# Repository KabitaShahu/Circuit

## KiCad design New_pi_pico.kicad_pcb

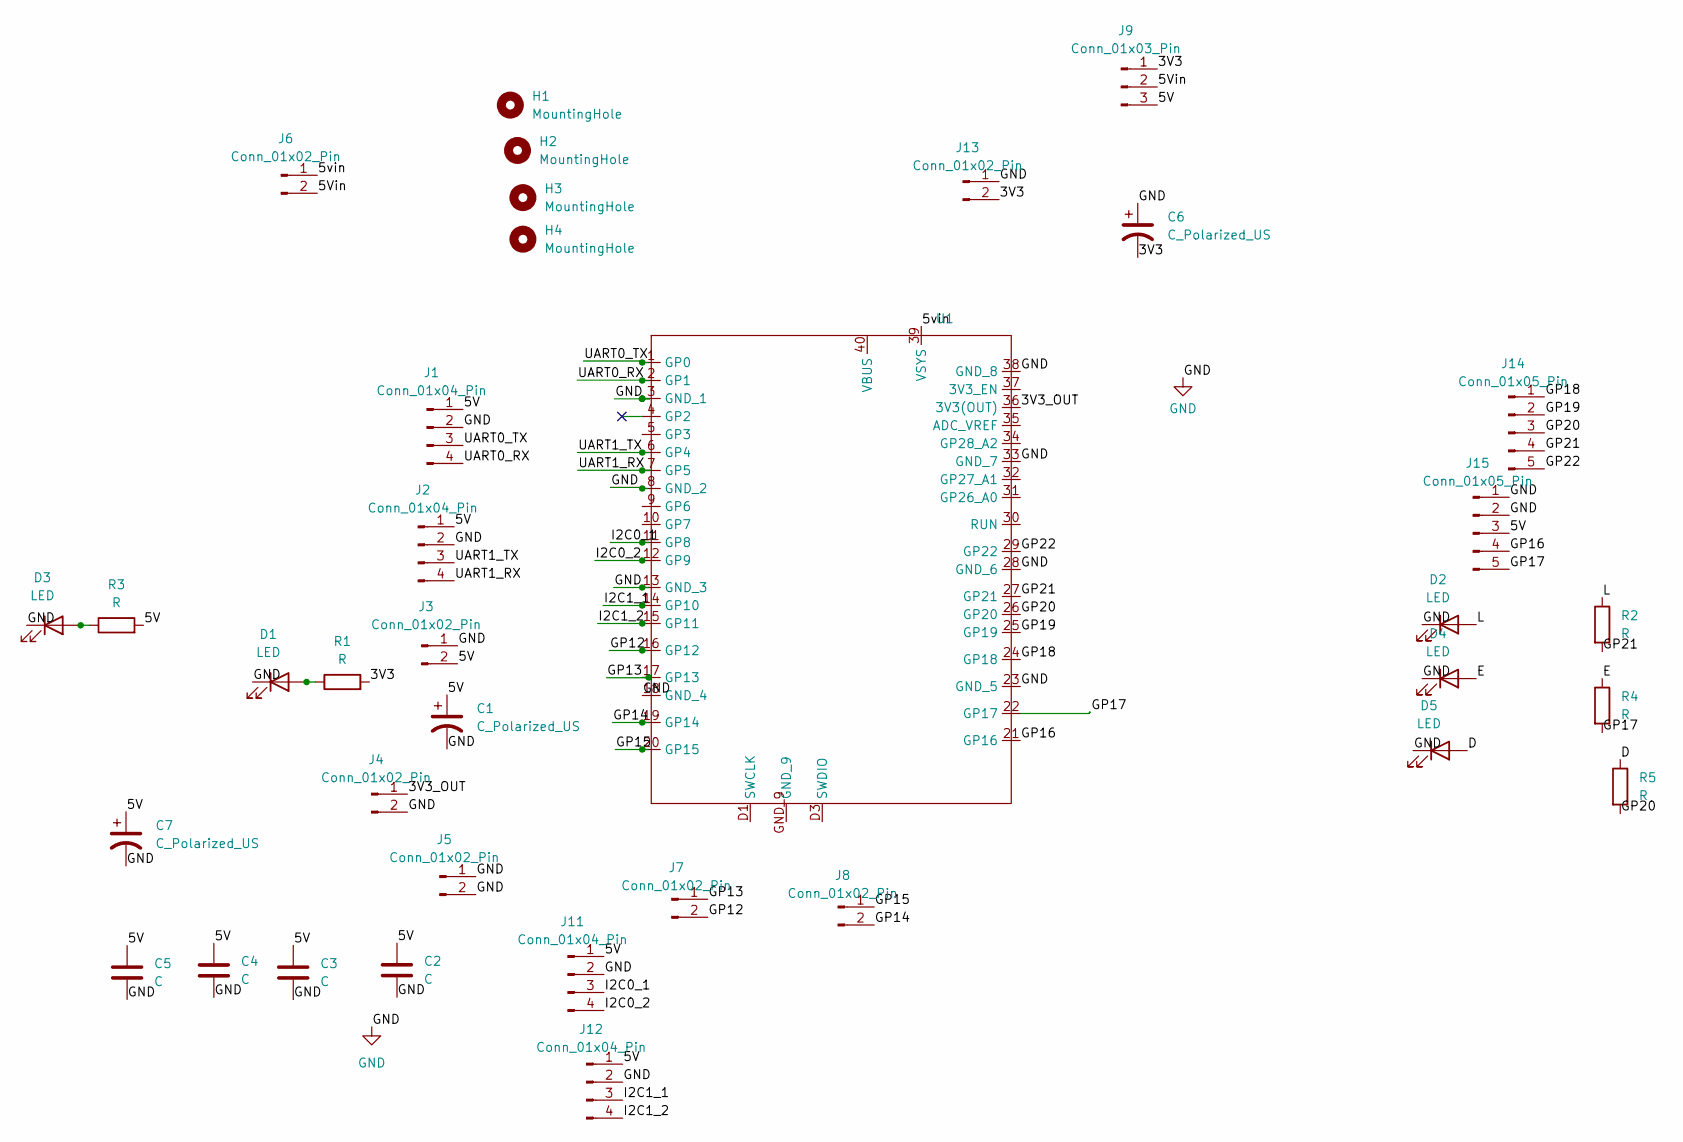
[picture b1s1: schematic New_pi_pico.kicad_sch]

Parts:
C1: C_Polarized_US; Capacitor_100uF
C2, C3, C4, C5: C; Capacitor_Disc_Small
C6, C7: C_Polarized_US; Capacitor_Disc_Small
D1, D2, D3, D4, D5: LED; LED_D3.0mm
H1, H2, H3, H4: MountingHole; MountingHole_3mm_Pad
J1, J2, J11, J12: Conn_01x04_Pin; jst_4
J3, J13: Conn_01x02_Pin; Connector_Bornier_2
J4, J5, J7, J8: Conn_01x02_Pin; JST_EH_B2B-EH-A_1x02_P2.50mm_Vertical
J6: Conn_01x02_Pin; KD1-101F_small
J9: Conn_01x03_Pin; SWITCH
J14, J15: Conn_01x05_Pin; JST_EH_B5B-EH-A_1x05_P2.50mm_Vertical
R1, R2, R3, R4, R5: R; Resistor_small
U1: pi_pico

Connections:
/3V3: C6.2, J9.1, J13.2, R1.2
/3V3_OUT: J4.1, U1.36 (3V3(OUT))
/5V: C1.1, C2.1, C3.1, C4.1, C5.1, C7.1, J1.1, J2.1, J3.2, J9.3, J11.1, J12.1, J15.3, R3.2
/5Vin: J6.2, J9.2
/5vin: J6.1, U1.39 (VSYS)
/D: D5.2 (A), R5.1
/E: D4.2 (A), R4.1
/GP12: J7.2, U1.16 (GP12)
/GP13: J7.1, U1.17 (GP13)
/GP14: J8.2, U1.19 (GP14)
/GP15: J8.1, U1.20 (GP15)
/GP16: J15.4, U1.21 (GP16)
/GP17: J15.5, R4.2, U1.22 (GP17)
/GP18: J14.1, U1.24 (GP18)
/GP19: J14.2, U1.25 (GP19)
/GP20: J14.3, R5.2, U1.26 (GP20)
/GP21: J14.4, R2.2, U1.27 (GP21)
/GP22: J14.5, U1.29 (GP22)
/I2C0_1: J11.3, U1.11 (GP8)
/I2C0_2: J11.4, U1.12 (GP9)
/I2C1_1: J12.3, U1.14 (GP10)
/I2C1_2: J12.4, U1.15 (GP11)
/L: D2.2 (A), R2.1
/UART0_RX: J1.4, U1.2 (GP1)
/UART0_TX: J1.3, U1.1 (GP0)
/UART1_RX: J2.4, U1.7 (GP5)
/UART1_TX: J2.3, U1.6 (GP4)
GND: C1.2, C2.2, C3.2, C4.2, C5.2, C6.1, C7.2, D1.1 (K), D2.1 (K), D3.1 (K), D4.1 (K), D5.1 (K), J1.2, J2.2, J3.1, J4.2, J5.1, J5.2, J11.2, J12.2, J13.1, J15.1, J15.2, U1.3 (GND_1), U1.8 (GND_2), U1.13 (GND_3), U1.18 (GND_4), U1.23 (GND_5), U1.28 (GND_6), U1.33 (GND_7), U1.38 (GND_8)
unnamed: D1.2 (A), R1.1
unnamed: D3.2 (A), R3.1

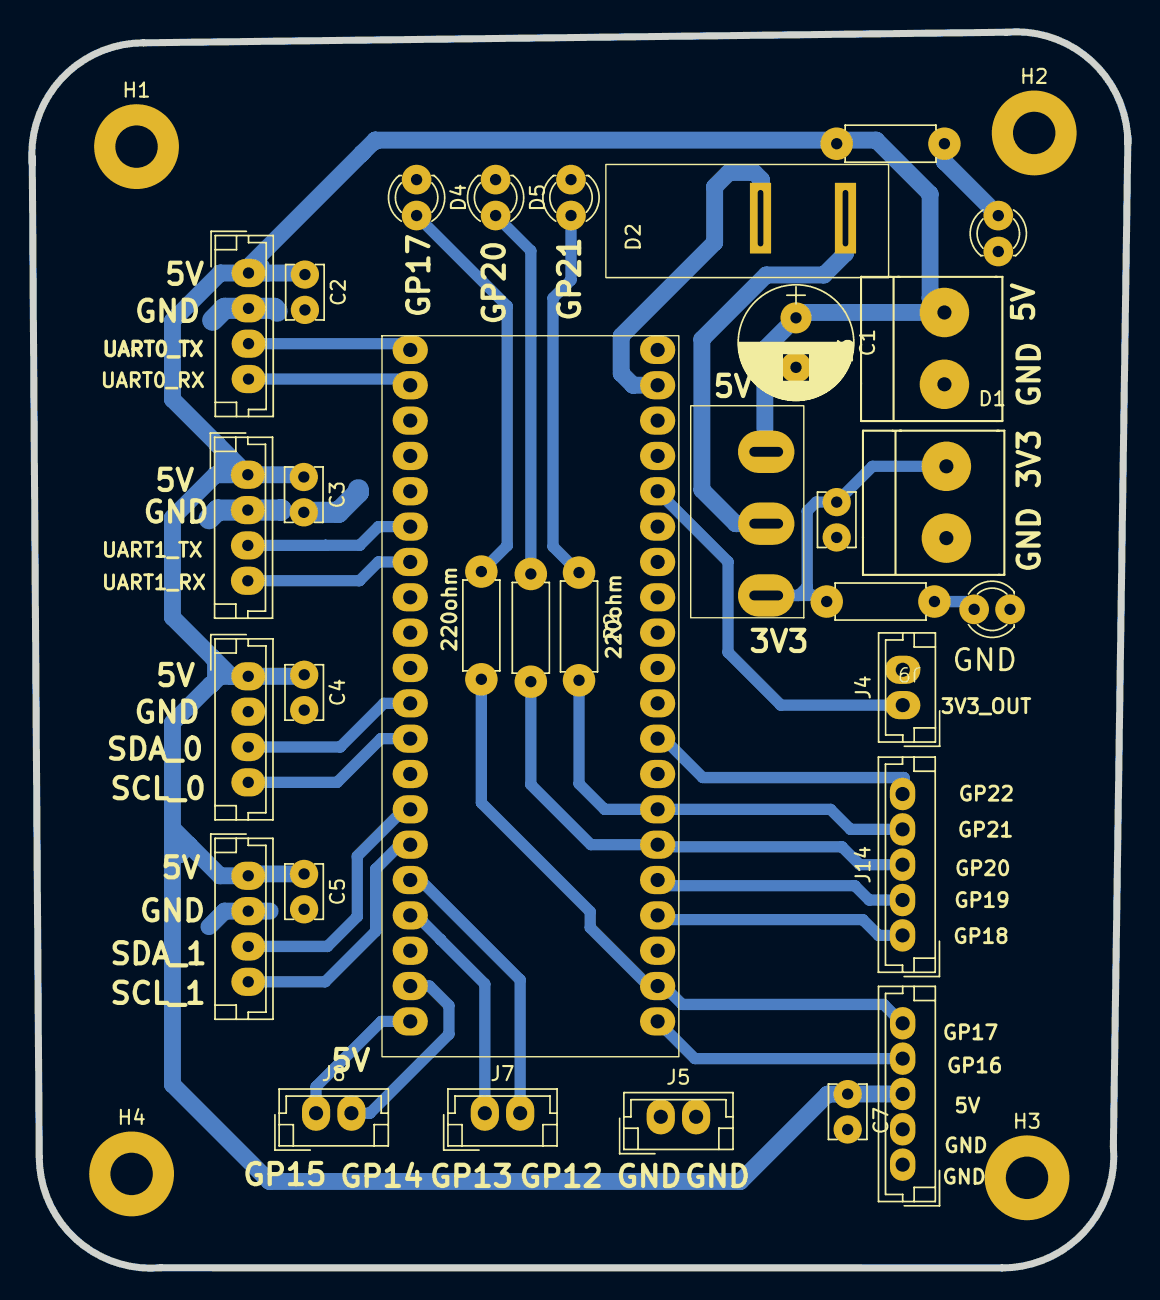
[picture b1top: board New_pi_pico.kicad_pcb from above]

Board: 2 copper layers, 77.5 x 87.5 mm, 36 parts (0 on the bottom side), 30 nets.

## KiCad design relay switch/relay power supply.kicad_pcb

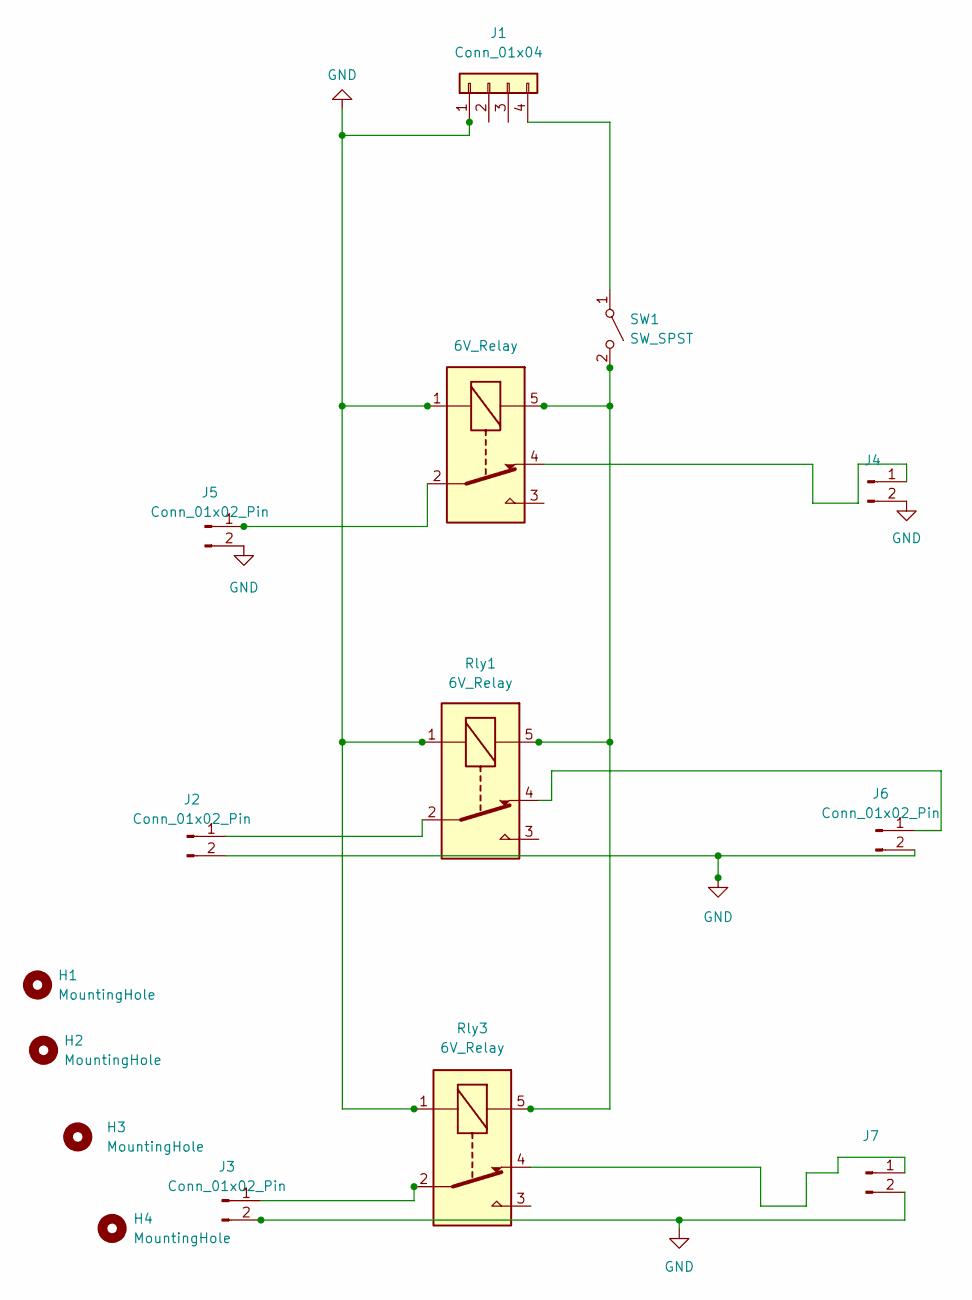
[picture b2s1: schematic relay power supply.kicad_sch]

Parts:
H1, H2, H3, H4: MountingHole; MountingHole_3mm_Pad
J1: Conn_01x04; jst_4
J2, J3, J4, J5, J6, J7: Conn_01x02_Pin; Solar_Connector
Rly1, Rly2, Rly3: 6V_Relay; HLS relay
SW1: SW_SPST; Solar_Connector

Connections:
GND: J1.1, J2.2, J3.2, J4.2, J5.2, J6.2, J7.2, Rly1.1, Rly2.1, Rly3.1
unnamed: J1.4, SW1.1 (A)
unnamed: J2.1, Rly1.2
unnamed: J3.1, Rly3.2
unnamed: J4.1, Rly2.4
unnamed: J5.1, Rly2.2
unnamed: J6.1, Rly1.4
unnamed: J7.1, Rly3.4
unnamed: Rly1.5, Rly2.5, Rly3.5, SW1.2 (B)

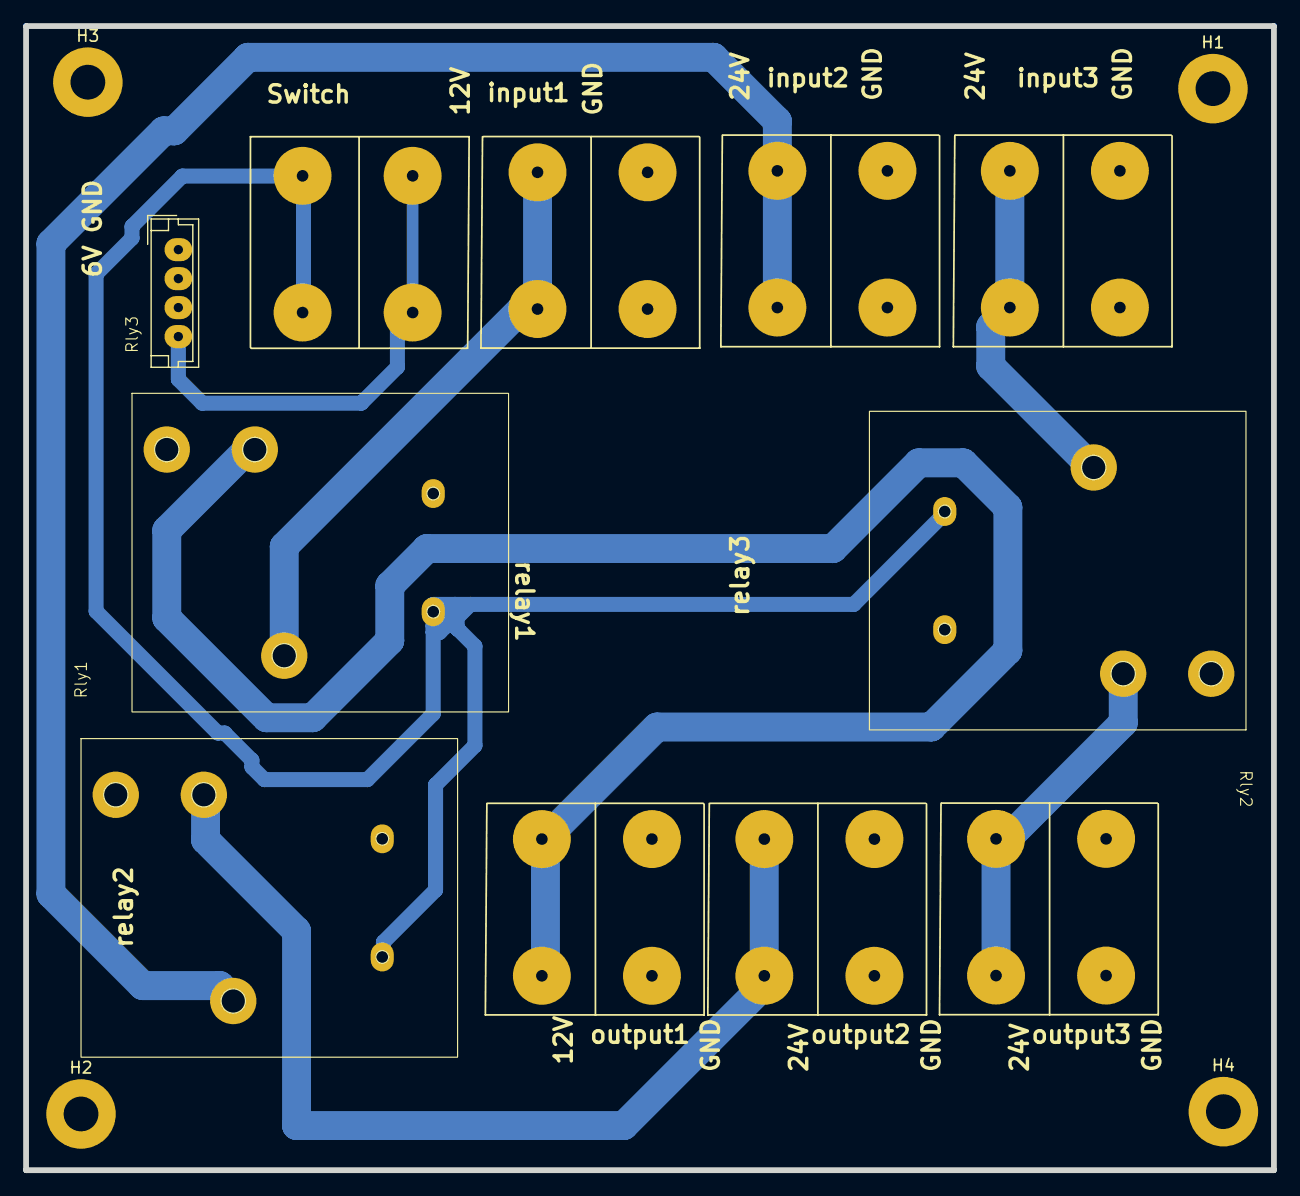
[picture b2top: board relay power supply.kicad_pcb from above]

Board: 2 copper layers, 107.7 x 98.8 mm, 15 parts (0 on the bottom side), 9 nets.

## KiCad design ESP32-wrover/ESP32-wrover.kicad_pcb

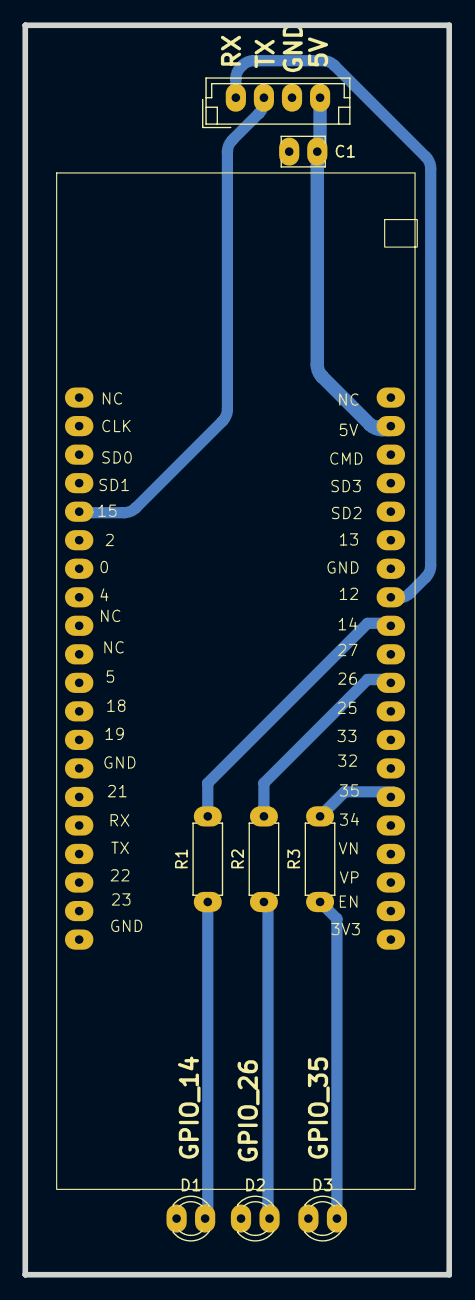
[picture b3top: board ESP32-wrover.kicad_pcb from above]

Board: 2 copper layers, 37.8 x 111.2 mm, 9 parts (0 on the bottom side), 10 nets.

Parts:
C1: C; Capacitor_Disc_Small
D1, D2, D3: LED; LED_D3.0mm
ESP32T1: ESP32_T18 - 3.0; ESP32_T18-3.0
J1: Conn_01x04_Pin; jst_4
R1, R2, R3: R; Resistor_small

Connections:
+5V: C1.1, ESP32T1.5V (CMD), J1.4
/1: D1.2 (A), R1.1
/2: D2.2 (A), R2.1
/3: D3.2 (A), R3.1
/LED1: ESP32T1.14 (GND), R1.2
/LED2: ESP32T1.26 (33), R2.2
/LED3: ESP32T1.35 (22), R3.2
/RX: ESP32T1.15 (4), J1.2
/TX: ESP32T1.12 (13), J1.1
GND: C1.2, D1.1 (K), D2.1 (K), D3.1 (K), ESP32T1.GND (SD3), J1.3

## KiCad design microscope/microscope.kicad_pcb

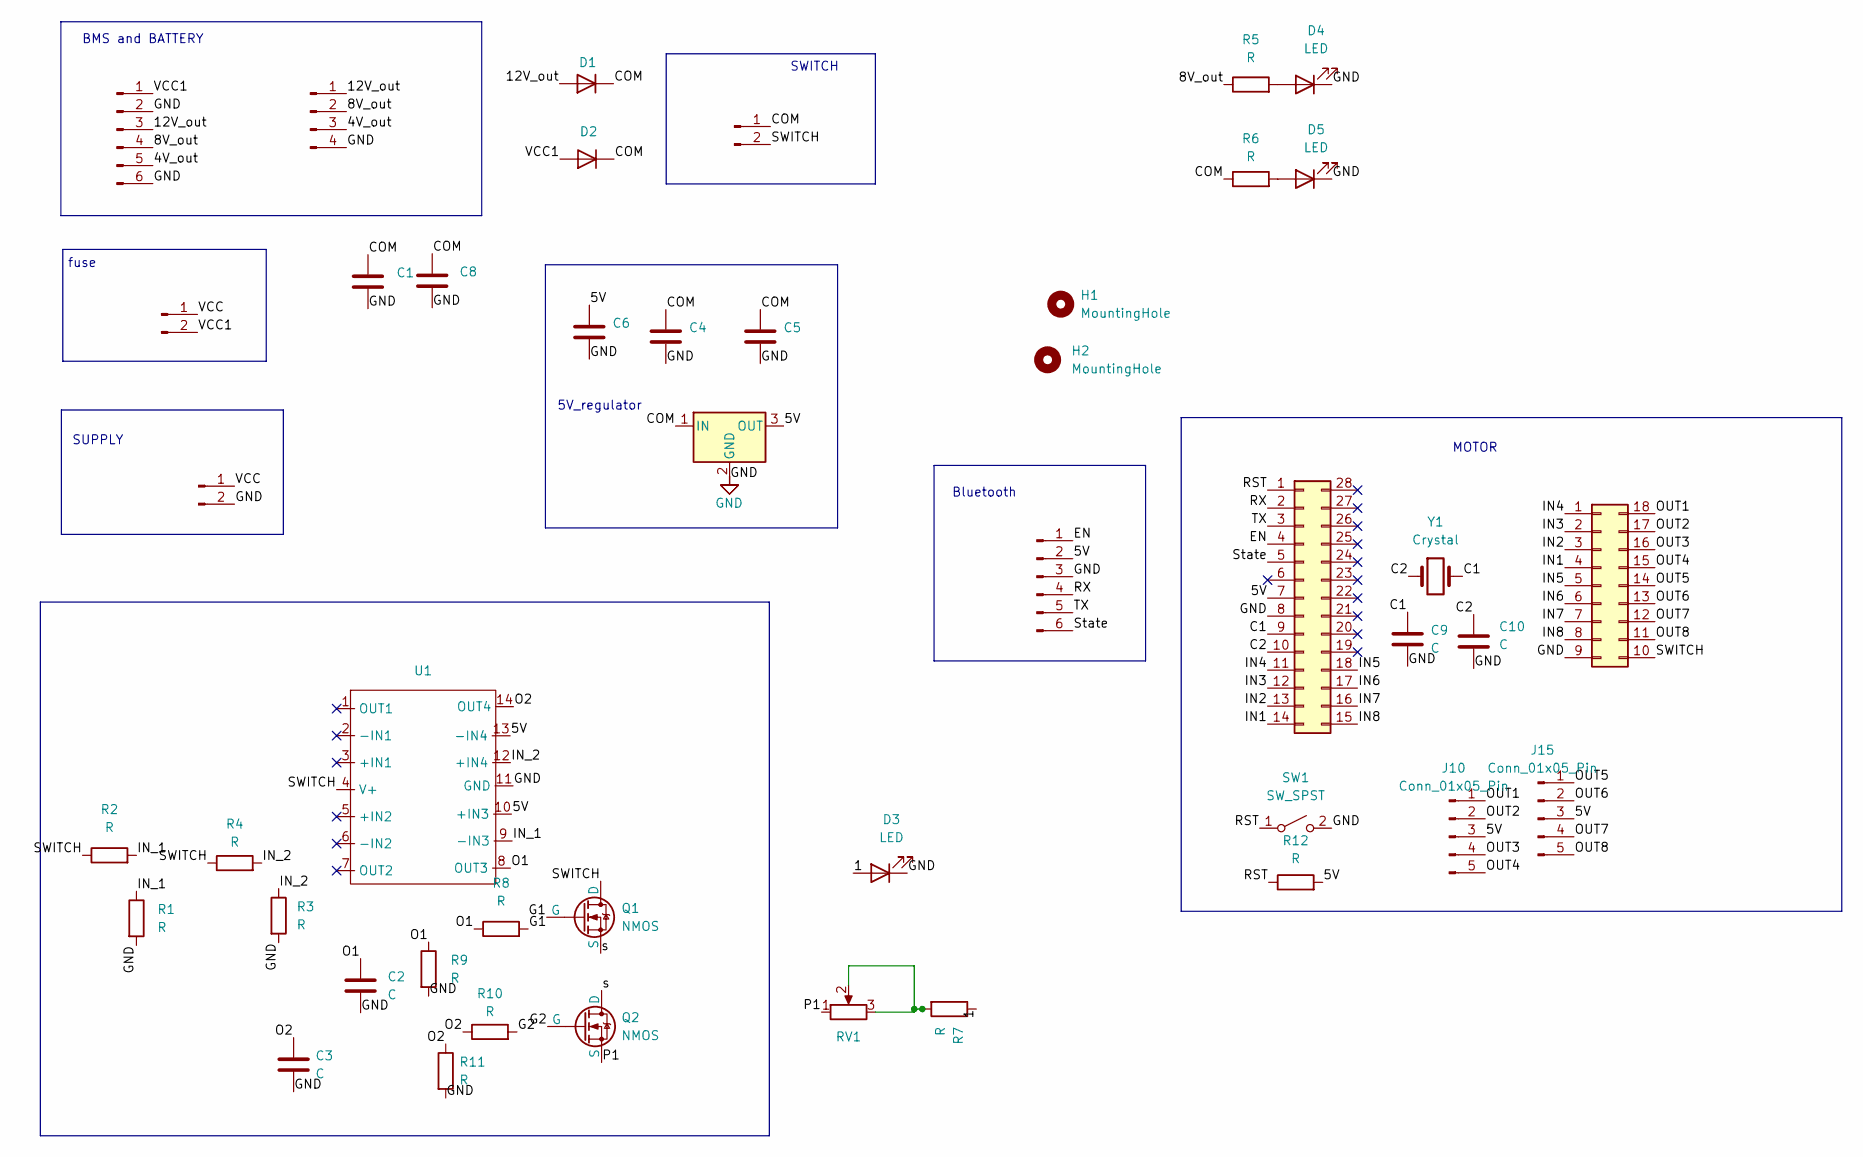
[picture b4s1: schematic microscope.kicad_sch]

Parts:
C1, C2, C3, C5, C9, C10: C; Capacitor_Disc_Small
C4, C8: C; Capacitor_100uF
C6: C; Capacitor_10uF
D1, D2: 1N914; Diode_Medium
D3, D4, D5: LED; bornier2
H1, H2: MountingHole; MountingHole_3mm
J1, J2, J6: Conn_01x02_Pin; bornier2
J5: Conn_01x04_Pin; new_5_jst_bournier
J7: Conn_02x14_Counter_Clockwise; DIP-28
J8: Conn_02x09_Counter_Clockwise; DIP-18_W7.62mm_LongPads
J9: Conn_01x06_Pin; PinHeader_1x06_P2.54mm_Vertical
J10, J15: Conn_01x05_Pin; new_5_jst_bournier
J11: Conn_01x06_Pin; BMS
Q1, Q2: NMOS; TO-220-3_Vertical
R1, R2, R3, R4, R5, R6, R8, R9, R10, R11, R12: R; Resistor_small
R7: R; R_Axial_DIN0516_L15.5mm_D5.0mm_P20.32mm_Horizontal
RV1: R_Potentiometer; bornier2
SW1: SW_SPST; Push_Button
U1: DIP-14_W7.62mm
U2: L7805; Voltage_Regulators
Y1: Crystal

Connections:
/1: D3.2 (A), R7.1
/4V_out: J5.3, J11.5
/5V: C6.1, J7.7, J9.2, J10.3, J15.3, R12.2, U1.10 (+IN3), U1.13 (-IN4), U2.3 (OUT)
/8V_out: J5.2, J11.4, R5.1
/12V_out: D1.2 (A), J5.1, J11.3
/C1: C9.1, J7.9, Y1.2
/C2: C10.1, J7.10, Y1.1
/COM: C1.1, C4.1, C5.1, C8.1, D1.1 (K), D2.1 (K), J6.1, R6.1, U2.1 (IN)
/EN: J7.4, J9.1
/G1: Q1.2 (G), R8.2
/G2: Q2.2 (G), R10.2
/IN1: J7.14, J8.4
/IN2: J7.13, J8.3
/IN3: J7.12, J8.2
/IN4: J7.11, J8.1
/IN5: J7.18, J8.5
/IN6: J7.17, J8.6
/IN7: J7.16, J8.7
/IN8: J7.15, J8.8
/IN_1: R1.1, R2.2, U1.9 (-IN3)
/IN_2: R3.1, R4.2, U1.12 (+IN4)
/O1: C2.1, R8.1, R9.1, U1.8 (OUT3)
/O2: C3.1, R10.1, R11.1, U1.14 (OUT4)
/OUT1: J8.18, J10.1
/OUT2: J8.17, J10.2
/OUT3: J8.16, J10.4
/OUT4: J8.15, J10.5
/OUT5: J8.14, J15.1
/OUT6: J8.13, J15.2
/OUT7: J8.12, J15.4
/OUT8: J8.11, J15.5
/P1: Q2.3 (S), RV1.1
/RST: J7.1, R12.1, SW1.1 (A)
/RX: J7.2, J9.4
/SWITCH: J6.2, J8.10, Q1.1 (D), R2.1, R4.1, U1.4 (V+)
/State: J7.5, J9.6
/TX: J7.3, J9.5
/VCC: J1.1, J2.1
/VCC1: D2.2 (A), J2.2, J11.1
/s: Q1.3 (S), Q2.1 (D)
GND: C1.2, C2.2, C3.2, C4.2, C5.2, C6.2, C8.2, C9.2, C10.2, D3.1 (K), D4.1 (K), D5.1 (K), J1.2, J5.4, J7.8, J8.9, J9.3, J11.2, J11.6, R1.2, R3.2, R9.2, R11.2, SW1.2 (B), U1.11 (GND), U2.2 (GND)
unnamed: D4.2 (A), R5.2
unnamed: D5.2 (A), R6.2
unnamed: R7.2, RV1.2, RV1.3

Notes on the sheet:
fuse
Bluetooth
MOTOR
SUPPLY
5V_regulator
SWITCH
BMS and BATTERY

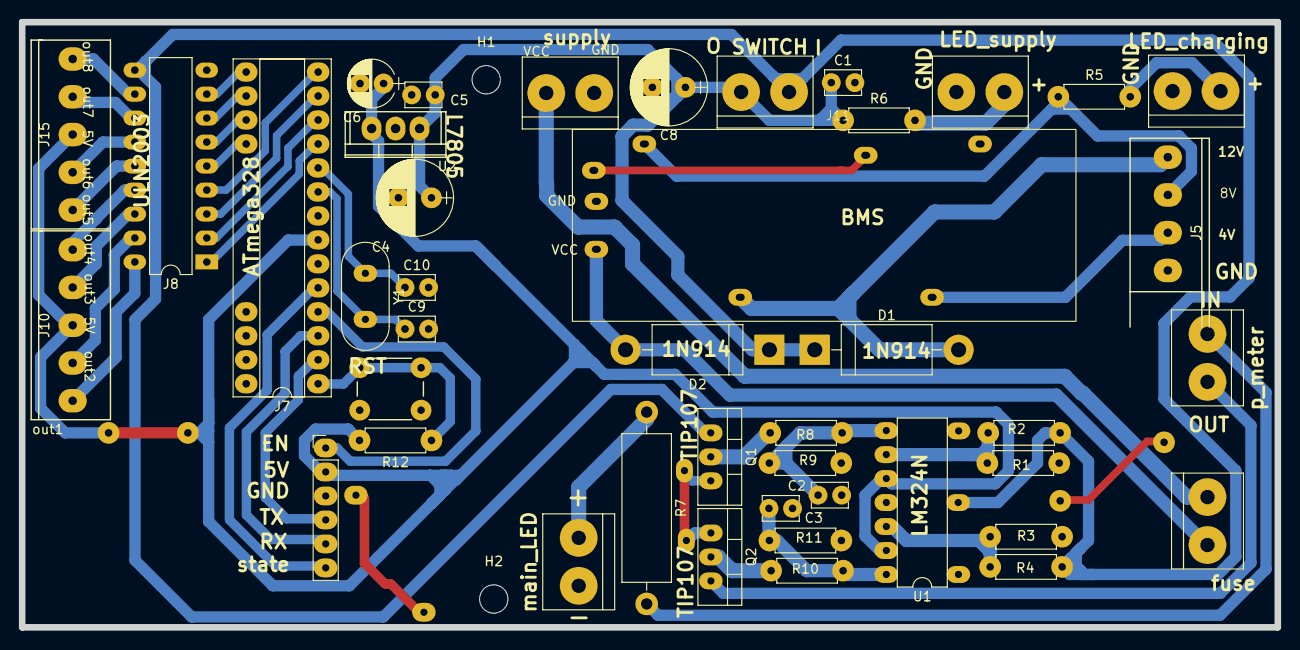
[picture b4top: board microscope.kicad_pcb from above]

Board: 2 copper layers, 133.0 x 64.1 mm, 45 parts (0 on the bottom side), 44 nets.

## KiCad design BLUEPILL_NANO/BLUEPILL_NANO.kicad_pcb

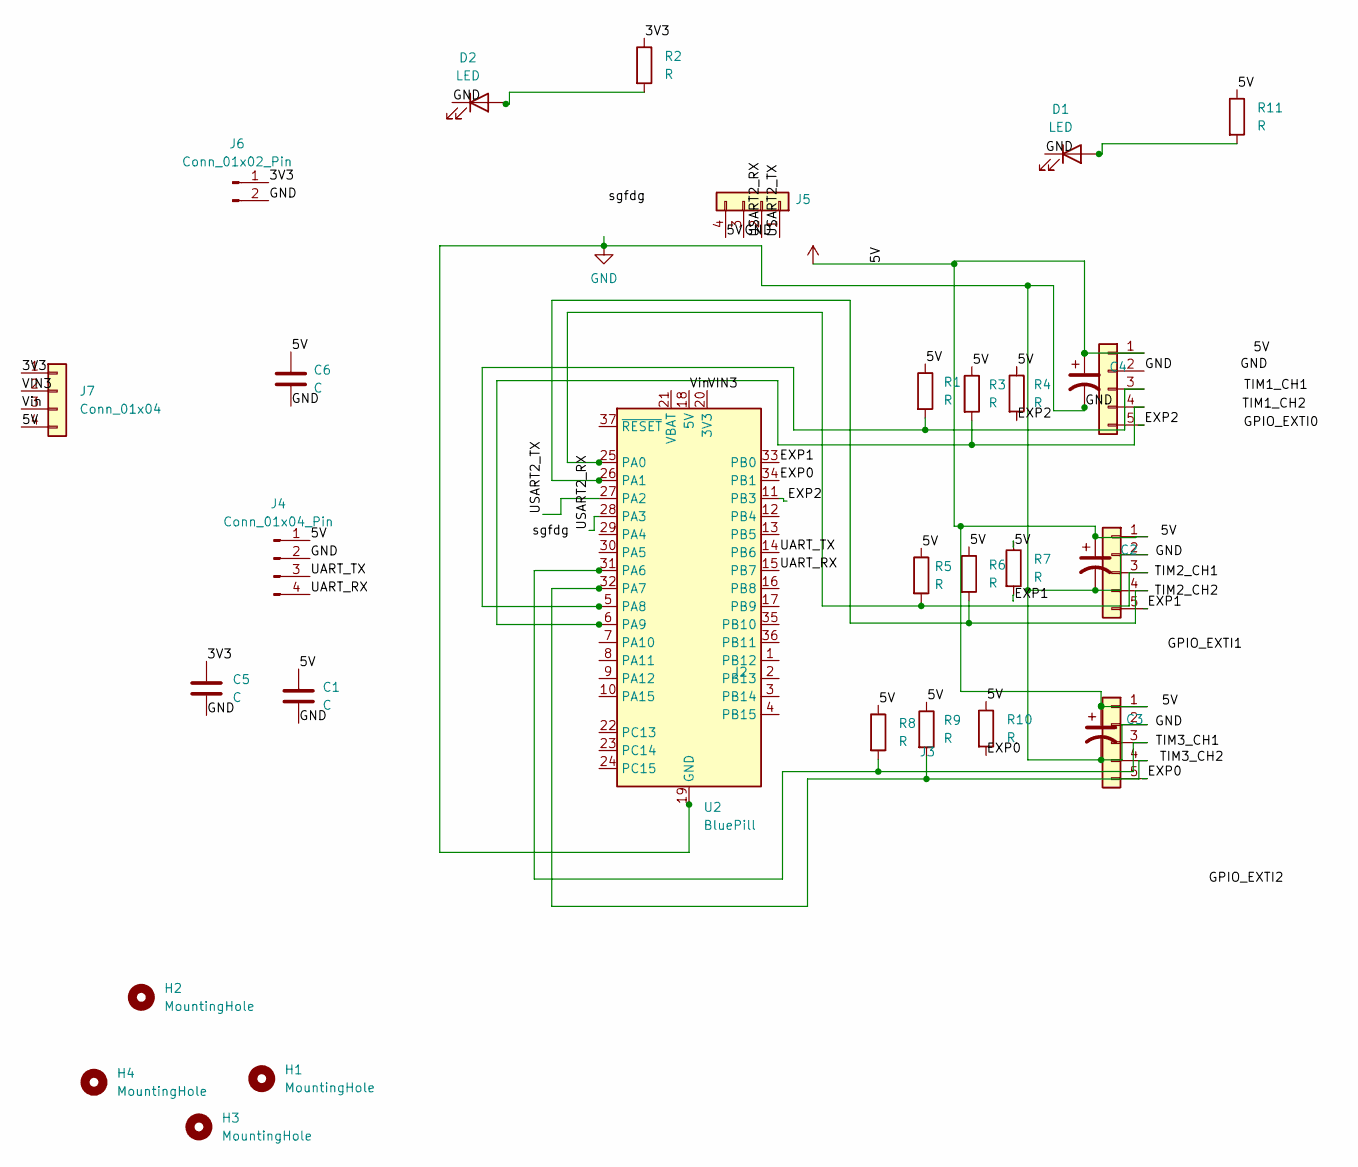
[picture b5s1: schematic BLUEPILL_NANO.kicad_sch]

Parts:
C1: C; Capacitor_100uF
C2, C3, C4: C_Polarized_US; Capacitor_Disc_Small
C5: C; Capacitor_10uF
C6: C; Capacitor_Disc_Small
D1, D2: LED; LED_D3.0mm
H1, H2, H3, H4: MountingHole; MountingHole_2.5mm_Pad
J1, J2, J3: Conn_01x05; JST_EH_B5B-EH-A_1x05_P2.50mm_Vertical
J4: Conn_01x04_Pin; jst_4
J5: Conn_01x04; jst_4
J6: Conn_01x02_Pin; JST_EH_B2B-EH-A_1x02_P2.50mm_Vertical
J7: Conn_01x04; PinHeader_1x04_P2.54mm_Vertical
R1, R2, R3, R4, R5, R6, R7, R8, R9, R10, R11: R; Resistor_small
U2: BluePill; STM32_BLUEPLL_MOD

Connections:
+5V: C1.1, C2.1, C3.1, C4.1, C6.1, J1.1, J2.1, J3.1, J4.1, J5.4, J7.4, R1.1, R3.1, R4.1, R5.1, R6.1, R7.1, R8.1, R9.1, R10.1, R11.1
/3V3: C5.1, J6.1, J7.1, R2.1
/EXP0: J3.5, R10.2, U2.34 (PB1)
/EXP1: J2.5, R7.2, U2.33 (PB0)
/EXP2: J1.5, R4.2, U2.11 (PB3)
/UART_RX: J4.4, U2.15 (PB7)
/UART_TX: J4.3, U2.14 (PB6)
/USART2_RX: J5.2, U2.28 (PA3)
/USART2_TX: J5.1, U2.27 (PA2)
/VIN3: J7.2, U2.20 (3V3), U2.38 (3V3)
/Vin: J7.3, U2.18 (5V)
GND: C1.2, C2.2, C3.2, C4.2, C5.2, C6.2, D1.1 (K), D2.1 (K), J1.2, J2.2, J3.2, J4.2, J5.3, J6.2, U2.19 (GND), U2.39 (GND), U2.40 (GND)
unnamed: D1.2 (A), R11.2
unnamed: D2.2 (A), R2.2
unnamed: J1.3, R1.2, U2.5 (PA8)
unnamed: J1.4, R3.2, U2.6 (PA9)
unnamed: J2.3, R5.2, U2.25 (PA0)
unnamed: J2.4, R6.2, U2.26 (PA1)
unnamed: J3.3, R8.2, U2.31 (PA6)
unnamed: J3.4, R9.2, U2.32 (PA7)

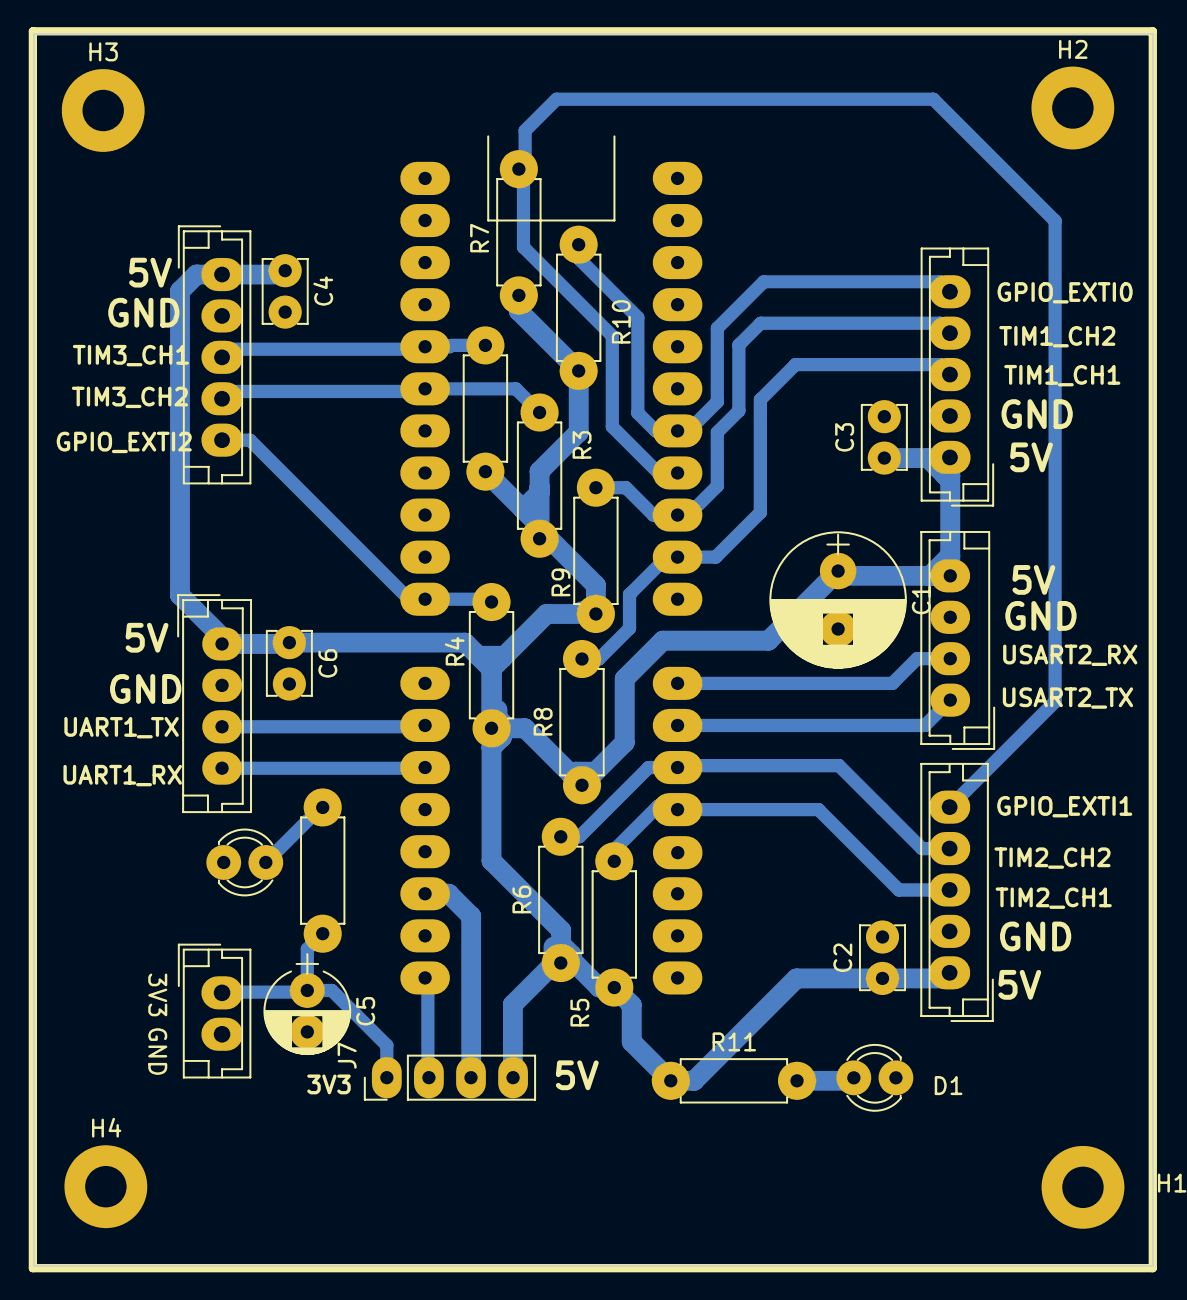
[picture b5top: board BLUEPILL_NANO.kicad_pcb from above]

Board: 2 copper layers, 67.5 x 74.4 mm, 31 parts (0 on the bottom side), 20 nets.

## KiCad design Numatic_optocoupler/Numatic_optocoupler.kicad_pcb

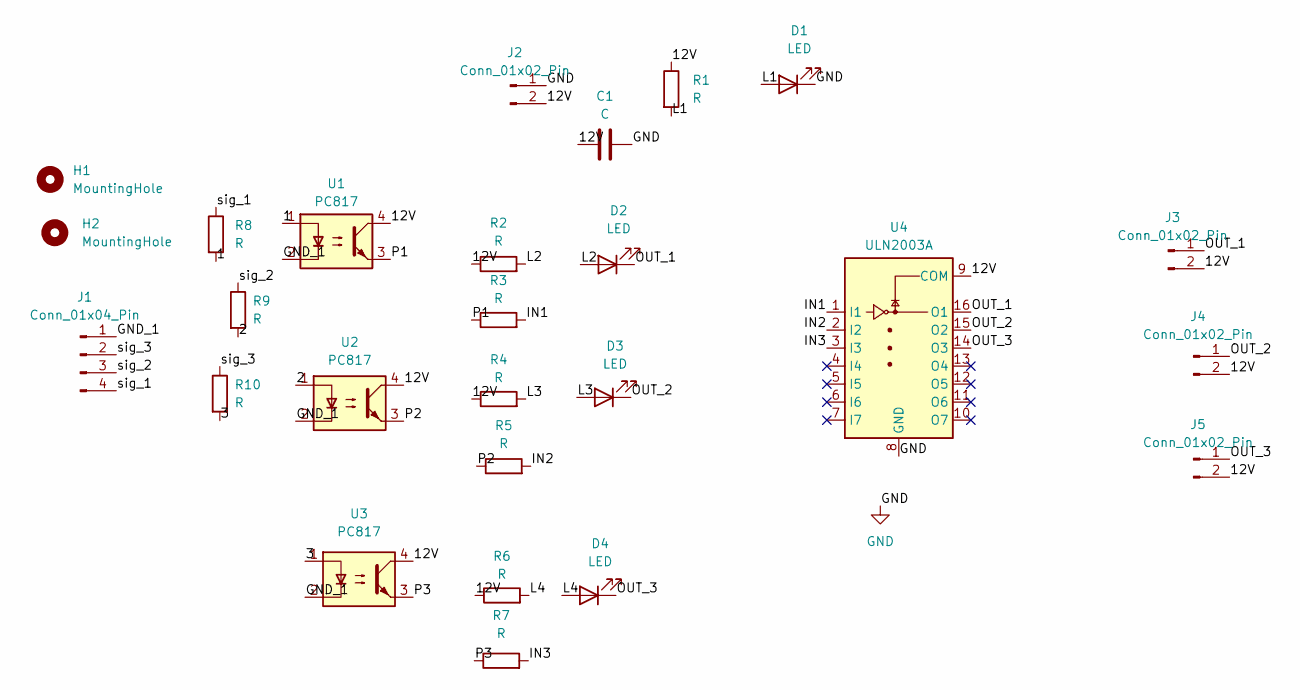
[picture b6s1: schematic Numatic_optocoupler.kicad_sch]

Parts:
C1: C; Capacitor_100uF
D1, D2, D3, D4: LED; LED_D3.0mm
H1, H2: MountingHole; MountingHole_3mm
J1: Conn_01x04_Pin; jst_4
J2, J3, J4, J5: Conn_01x02_Pin; bornier2
R1, R2, R3, R4, R5, R6, R7, R8, R9, R10: R; Resistor_small
U1, U2, U3: PC817; DIP-4_W7.62mm
U4: ULN2003A; DIP-16_W7.62mm_LongPads

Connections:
/1: R8.2, U1.1
/2: R9.2, U2.1
/3: R10.2, U3.1
/12V: C1.2, J2.2, J3.2, J4.2, J5.2, R1.1, R2.1, R4.1, R6.1, U1.4, U2.4, U3.4, U4.9 (COM)
/GND_1: J1.1, U1.2, U2.2, U3.2
/IN1: R3.2, U4.1 (I1)
/IN2: R5.2, U4.2 (I2)
/IN3: R7.2, U4.3 (I3)
/L1: D1.2 (A), R1.2
/L2: D2.2 (A), R2.2
/L3: D3.2 (A), R4.2
/L4: D4.2 (A), R6.2
/OUT_1: D2.1 (K), J3.1, U4.16 (O1)
/OUT_2: D3.1 (K), J4.1, U4.15 (O2)
/OUT_3: D4.1 (K), J5.1, U4.14 (O3)
/P1: R3.1, U1.3
/P2: R5.1, U2.3
/P3: R7.1, U3.3
/sig_1: J1.4, R8.1
/sig_2: J1.3, R9.1
/sig_3: J1.2, R10.1
GND: C1.1, D1.1 (K), J2.1, U4.8 (GND)

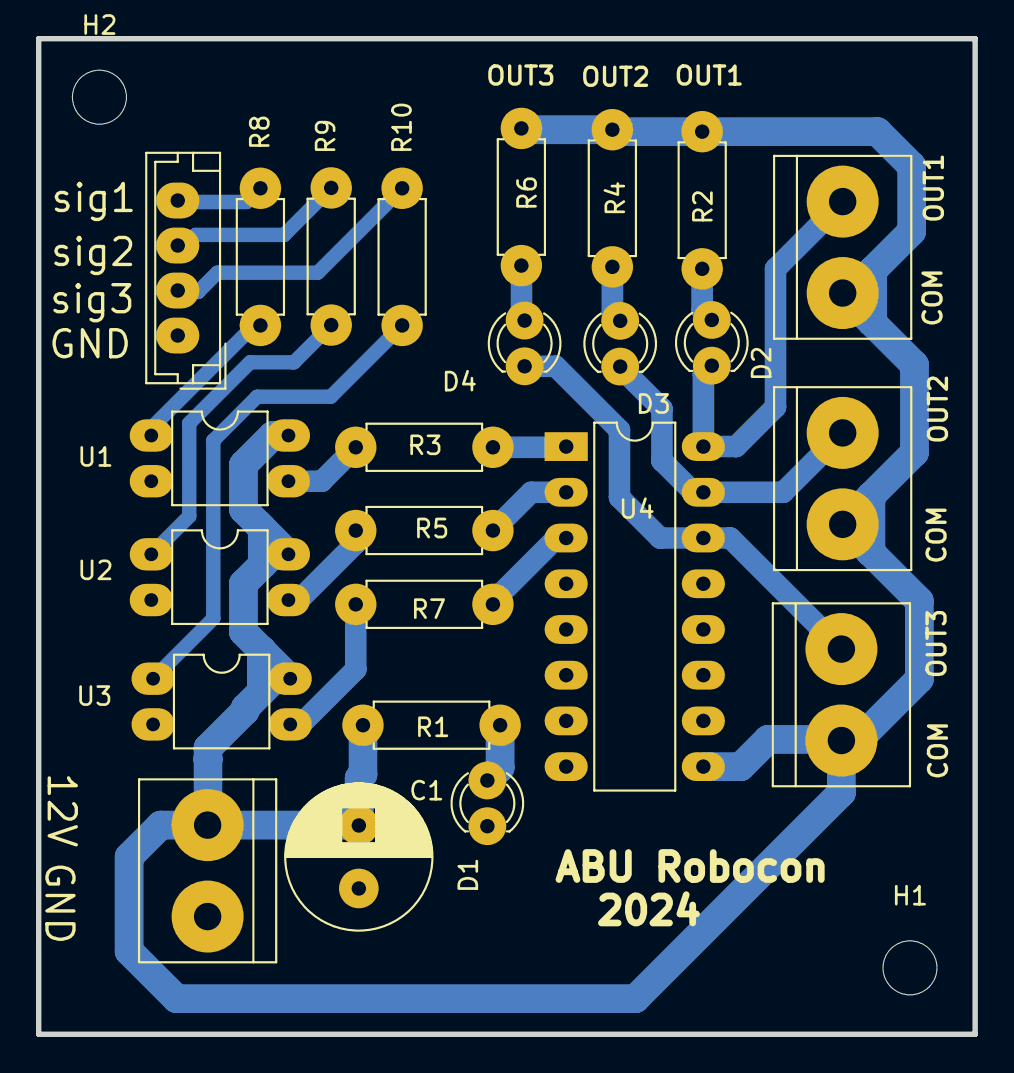
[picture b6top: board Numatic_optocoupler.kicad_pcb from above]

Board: 2 copper layers, 52.0 x 55.3 mm, 26 parts (0 on the bottom side), 22 nets.

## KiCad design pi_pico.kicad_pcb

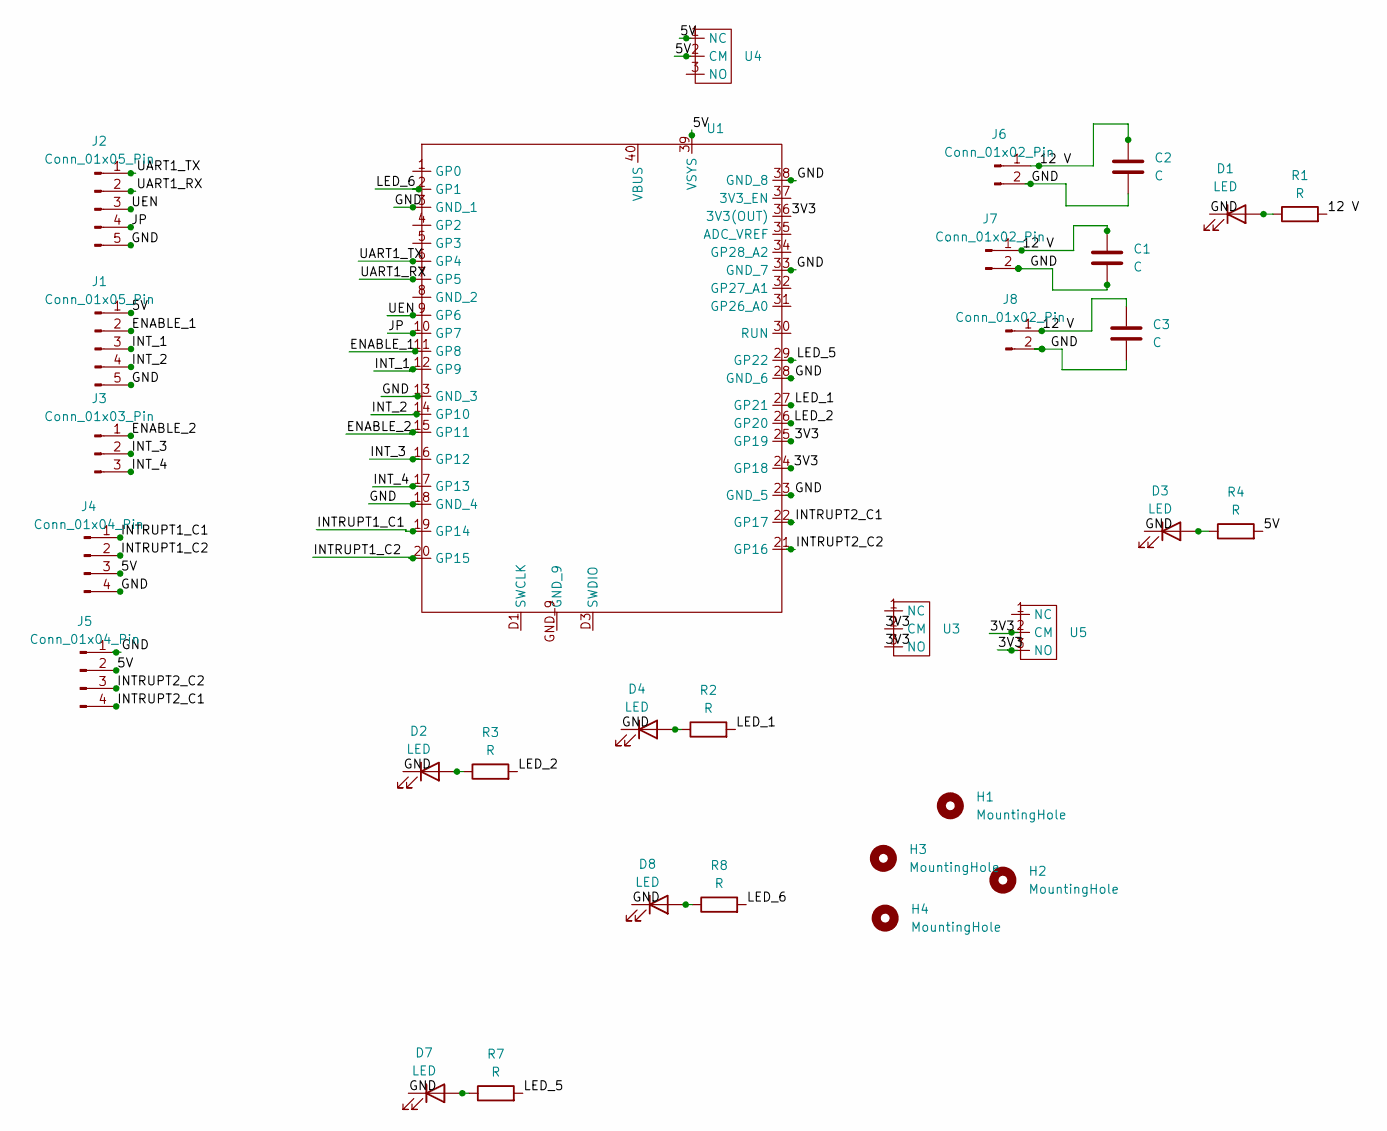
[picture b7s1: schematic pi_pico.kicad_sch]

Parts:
C1, C2, C3: C; Capacitor_100uF
D1, D2, D3, D4, D7, D8: LED; LED_D3.0mm
H1, H2, H3, H4: MountingHole; MountingHole_3.5mm
J1, J2: Conn_01x05_Pin; JST_EH_B5B-EH-A_1x05_P2.50mm_Vertical
J3: Conn_01x03_Pin; JST_EH_B3B-EH-A_1x03_P2.50mm_Vertical
J4, J5: Conn_01x04_Pin; JST_EH_B4B-EH-A_1x04_P2.50mm_Vertical
J6, J7, J8: Conn_01x02_Pin; bornier2
R1, R2, R3, R4, R7, R8: R; Resistor_small
U1: pi_pico
U3, U4, U5: SWITCH

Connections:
/3V3: U1.24 (GP18), U1.25 (GP19), U1.36 (3V3(OUT)), U3.2 (CM), U3.3 (NO), U5.2 (CM), U5.3 (NO)
/5V: J1.1, J4.3, J5.2, R4.2, U1.39 (VSYS), U4.1 (NC), U4.2 (CM)
/12 V: C1.1, C2.1, C3.1, J6.1, J7.1, J8.1, R1.2
/ENABLE_1: J1.2, U1.11 (GP8)
/ENABLE_2: J3.1, U1.15 (GP11)
/GND: C1.2, C2.2, C3.2, D1.1 (K), D2.1 (K), D3.1 (K), D4.1 (K), D7.1 (K), D8.1 (K), J1.5, J2.5, J4.4, J5.1, J6.2, J7.2, J8.2, U1.3 (GND_1), U1.13 (GND_3), U1.18 (GND_4), U1.23 (GND_5), U1.28 (GND_6), U1.33 (GND_7), U1.38 (GND_8)
/INTRUPT1_C1: J4.1, U1.19 (GP14)
/INTRUPT1_C2: J4.2, U1.20 (GP15)
/INTRUPT2_C1: J5.4, U1.22 (GP17)
/INTRUPT2_C2: J5.3, U1.21 (GP16)
/INT_1: J1.3, U1.12 (GP9)
/INT_2: J1.4, U1.14 (GP10)
/INT_3: J3.2, U1.16 (GP12)
/INT_4: J3.3, U1.17 (GP13)
/JP: J2.4, U1.10 (GP7)
/LED_1: R2.2, U1.27 (GP21)
/LED_2: R3.2, U1.26 (GP20)
/LED_5: R7.2, U1.29 (GP22)
/LED_6: R8.2, U1.2 (GP1)
/UART1_RX: J2.2, U1.7 (GP5)
/UART1_TX: J2.1, U1.6 (GP4)
/UEN: J2.3, U1.9 (GP6)
unnamed: D1.2 (A), R1.1
unnamed: D2.2 (A), R3.1
unnamed: D3.2 (A), R4.1
unnamed: D4.2 (A), R2.1
unnamed: D7.2 (A), R7.1
unnamed: D8.2 (A), R8.1
